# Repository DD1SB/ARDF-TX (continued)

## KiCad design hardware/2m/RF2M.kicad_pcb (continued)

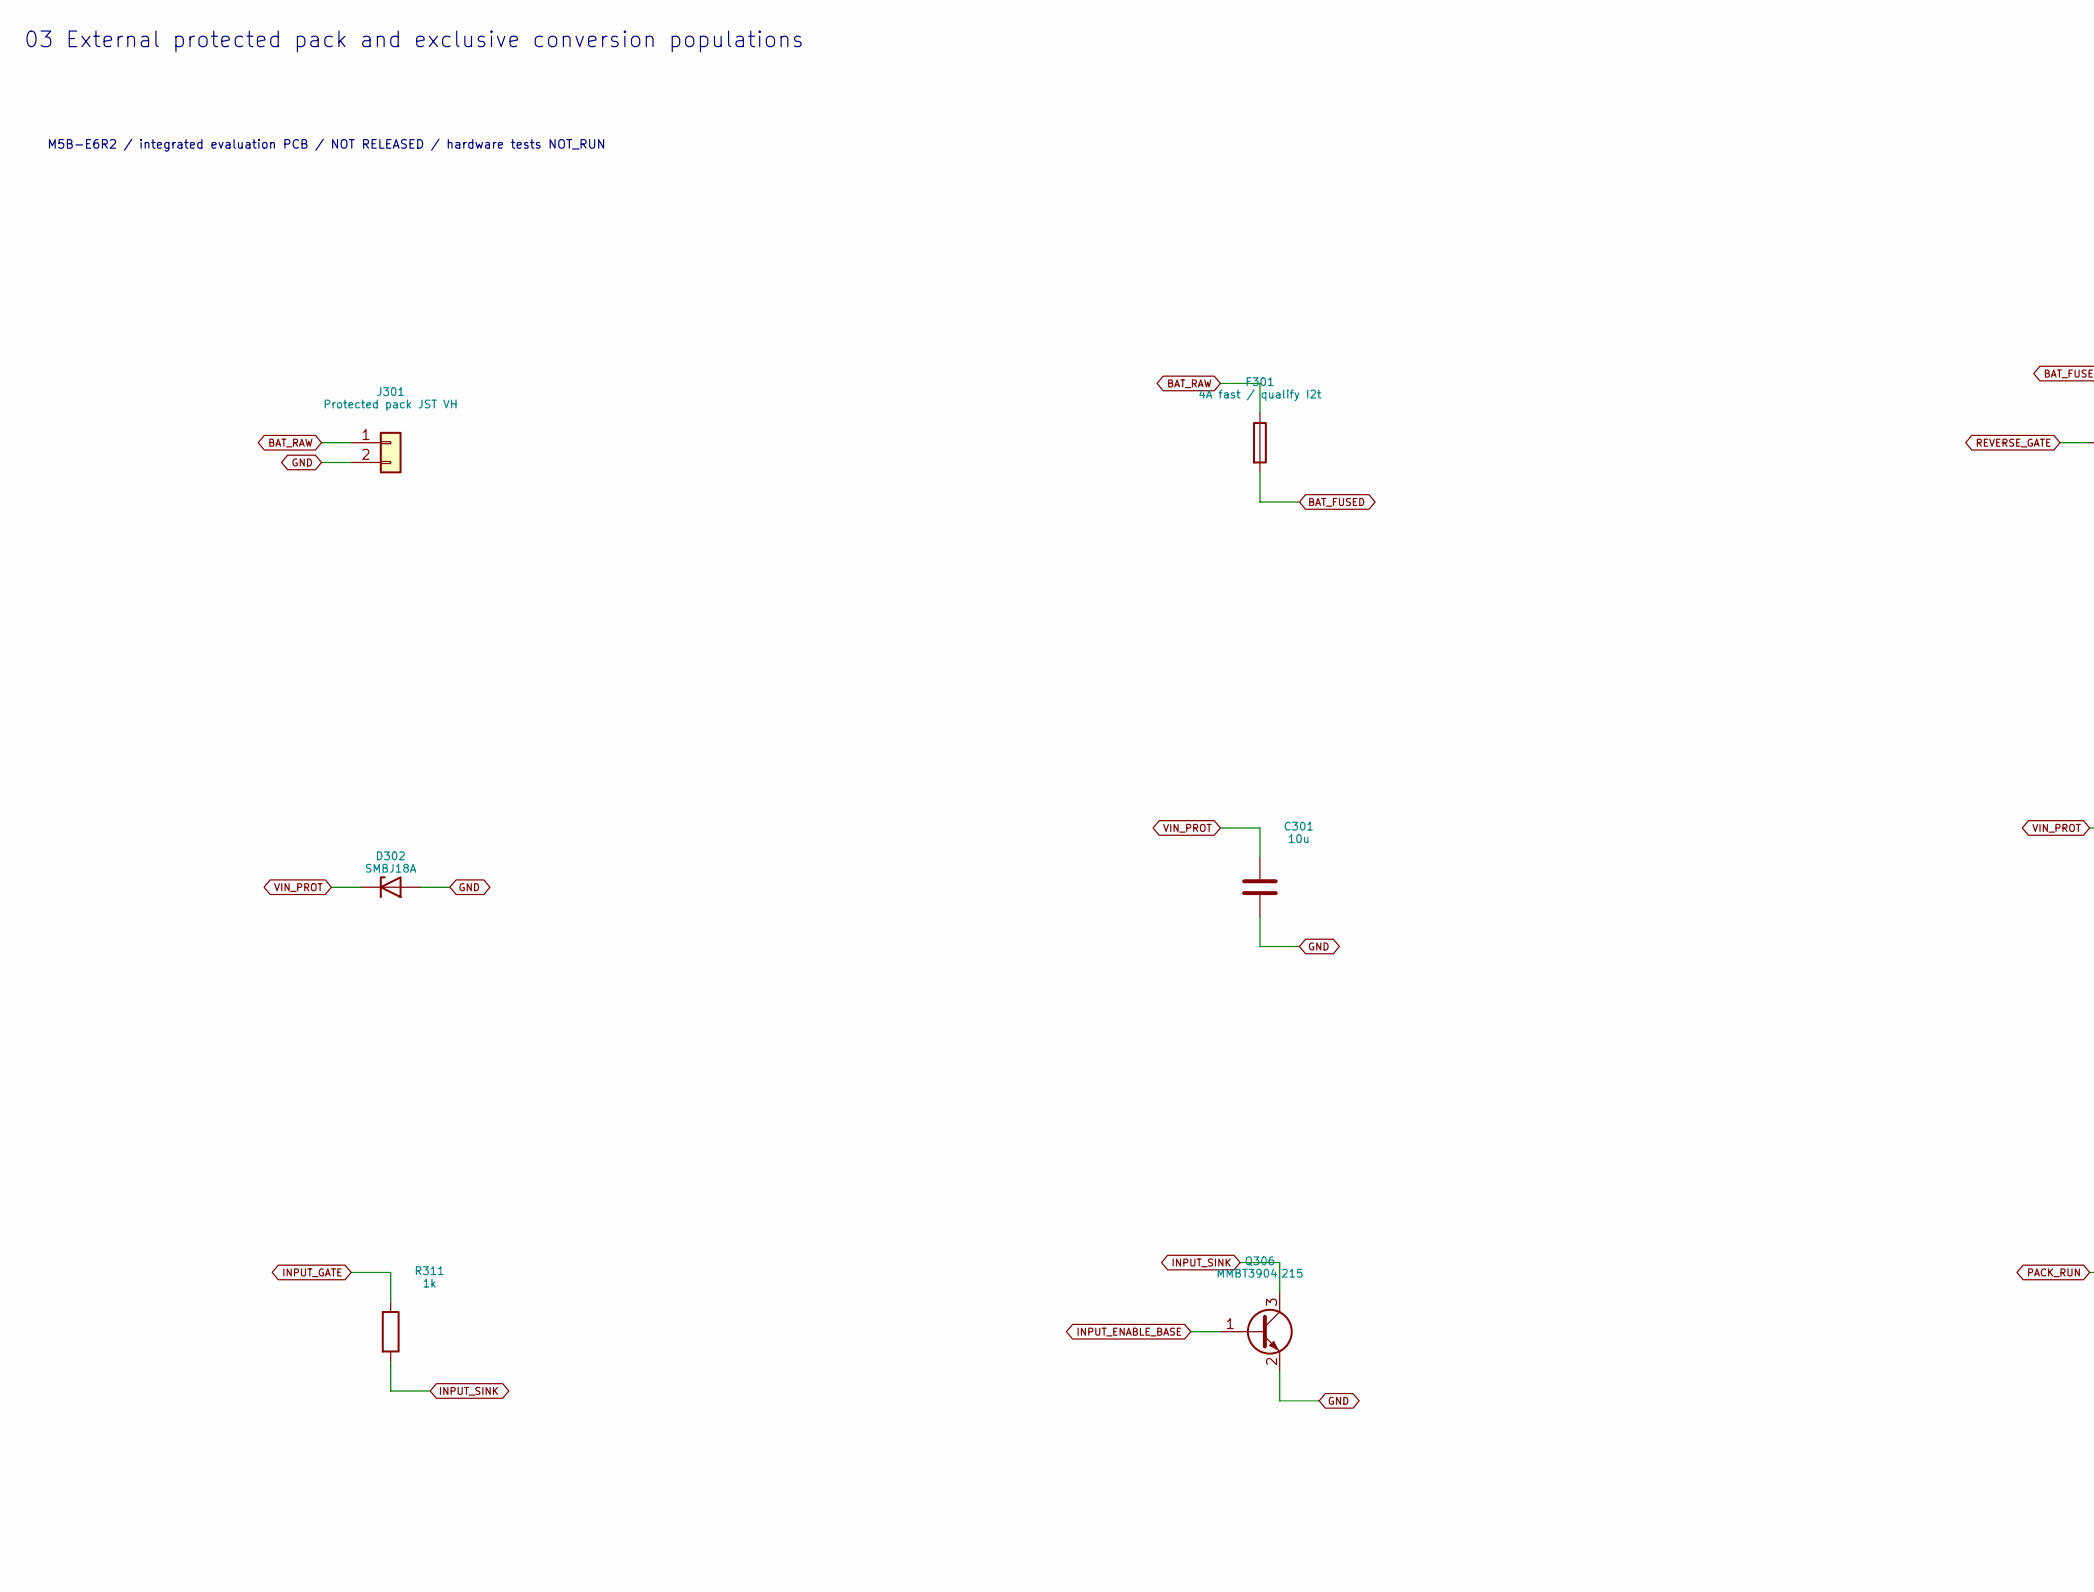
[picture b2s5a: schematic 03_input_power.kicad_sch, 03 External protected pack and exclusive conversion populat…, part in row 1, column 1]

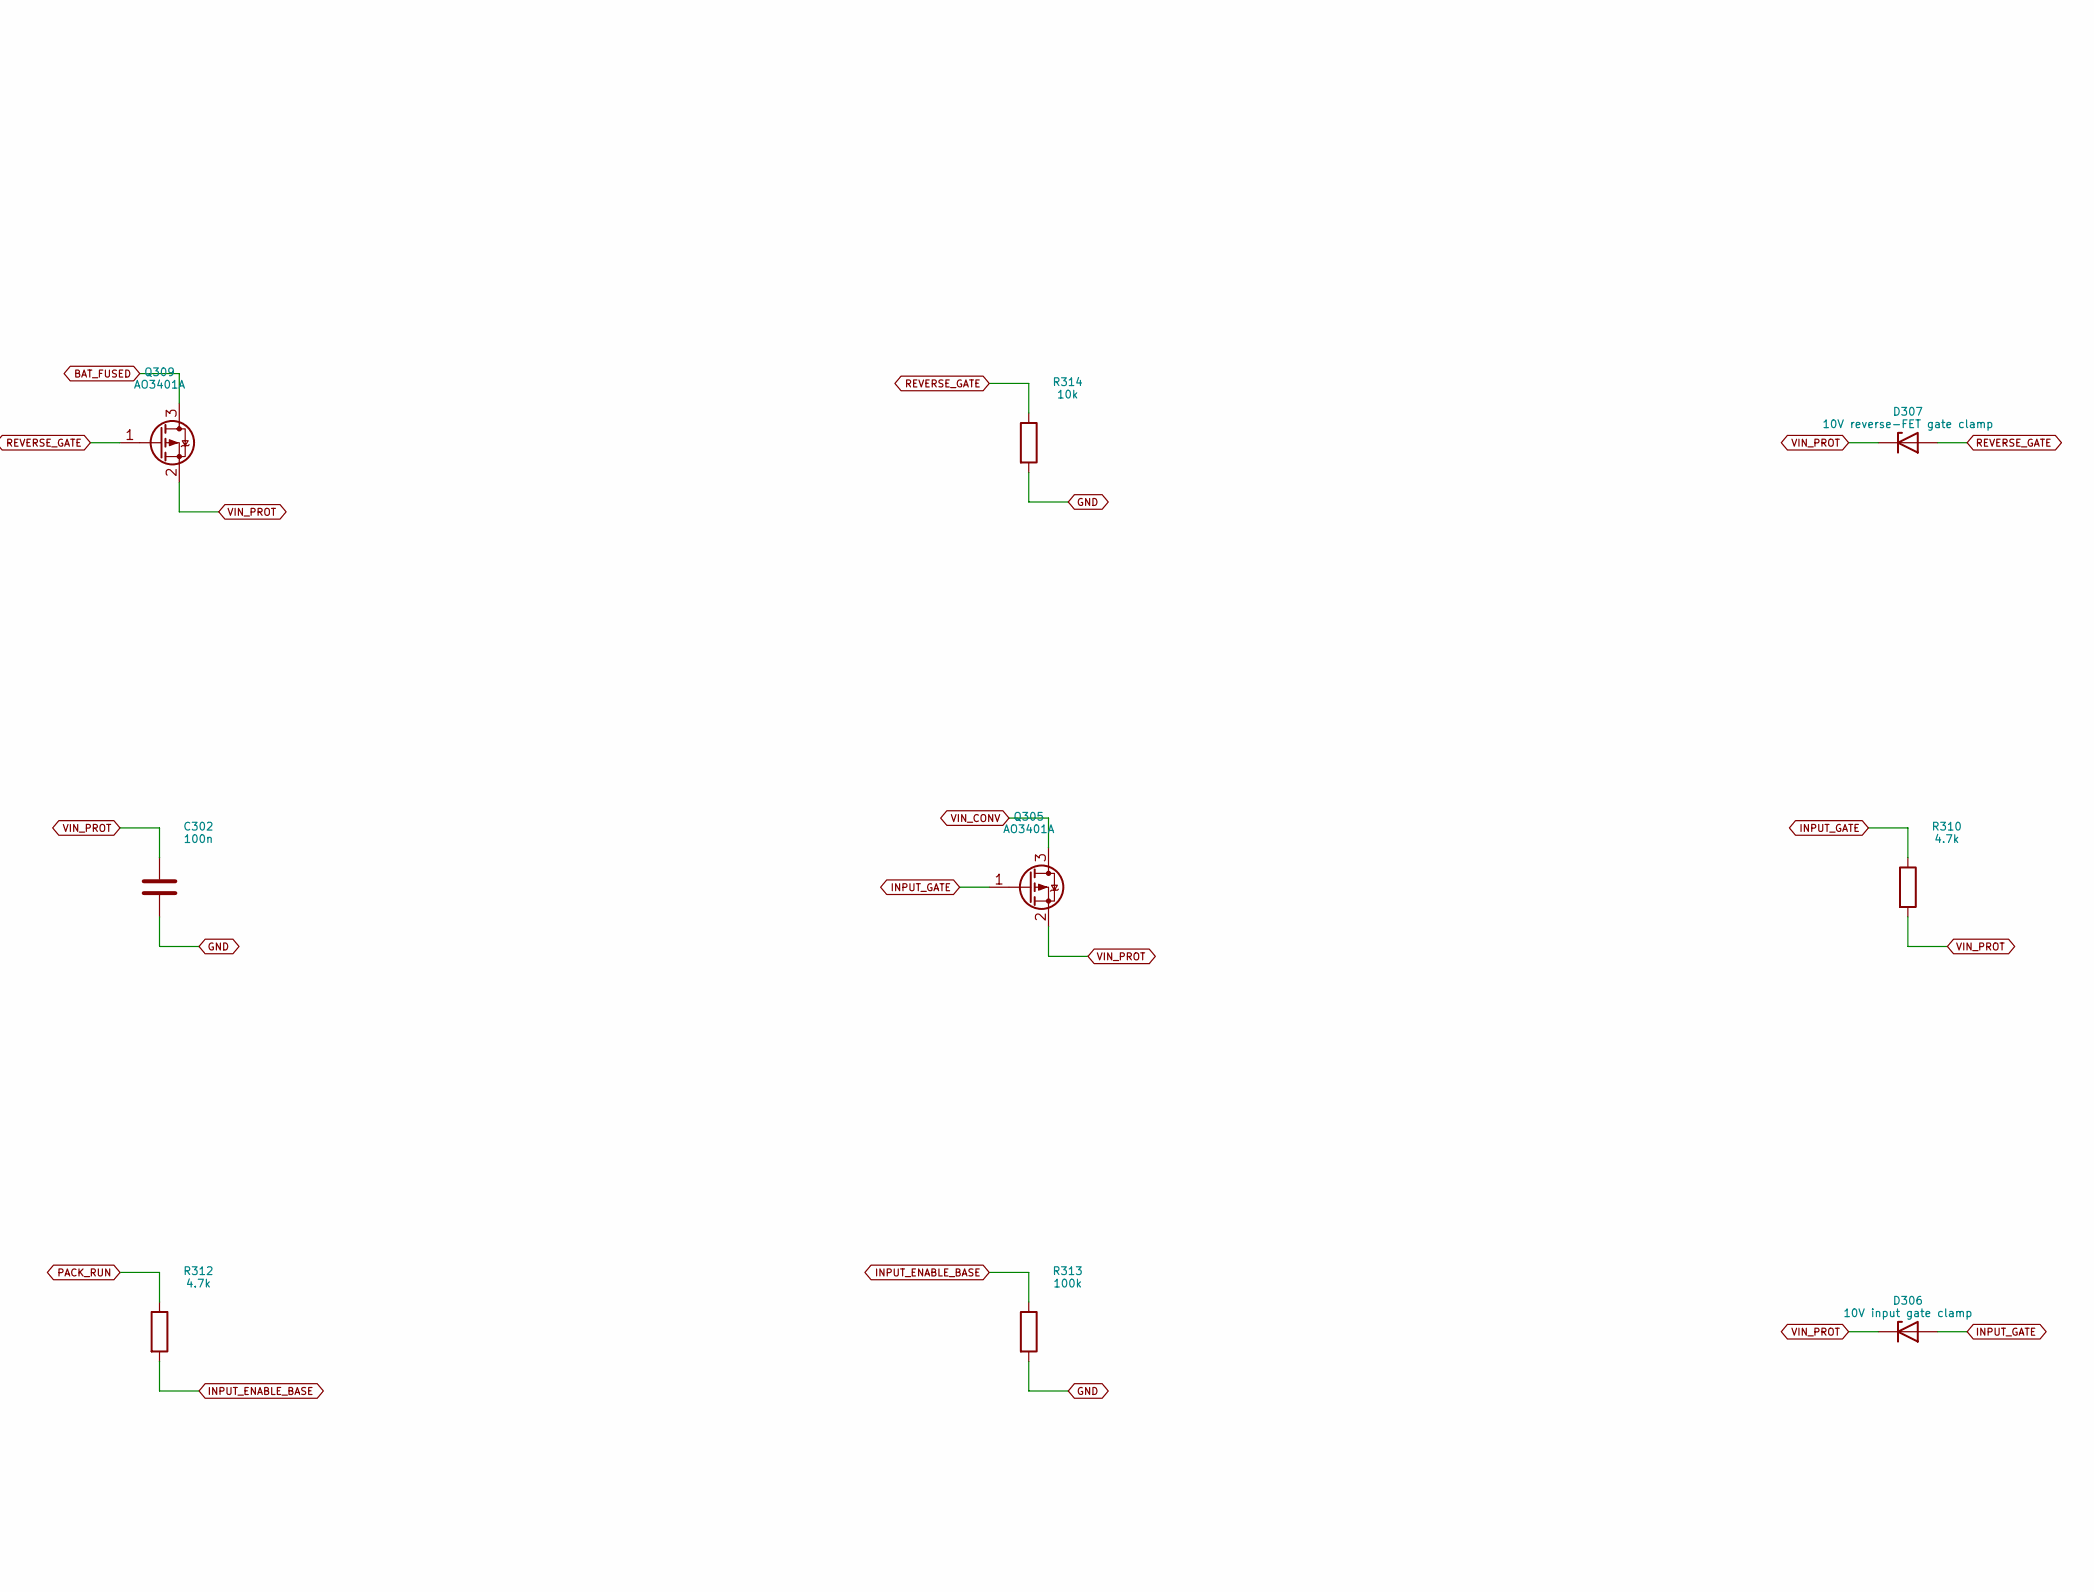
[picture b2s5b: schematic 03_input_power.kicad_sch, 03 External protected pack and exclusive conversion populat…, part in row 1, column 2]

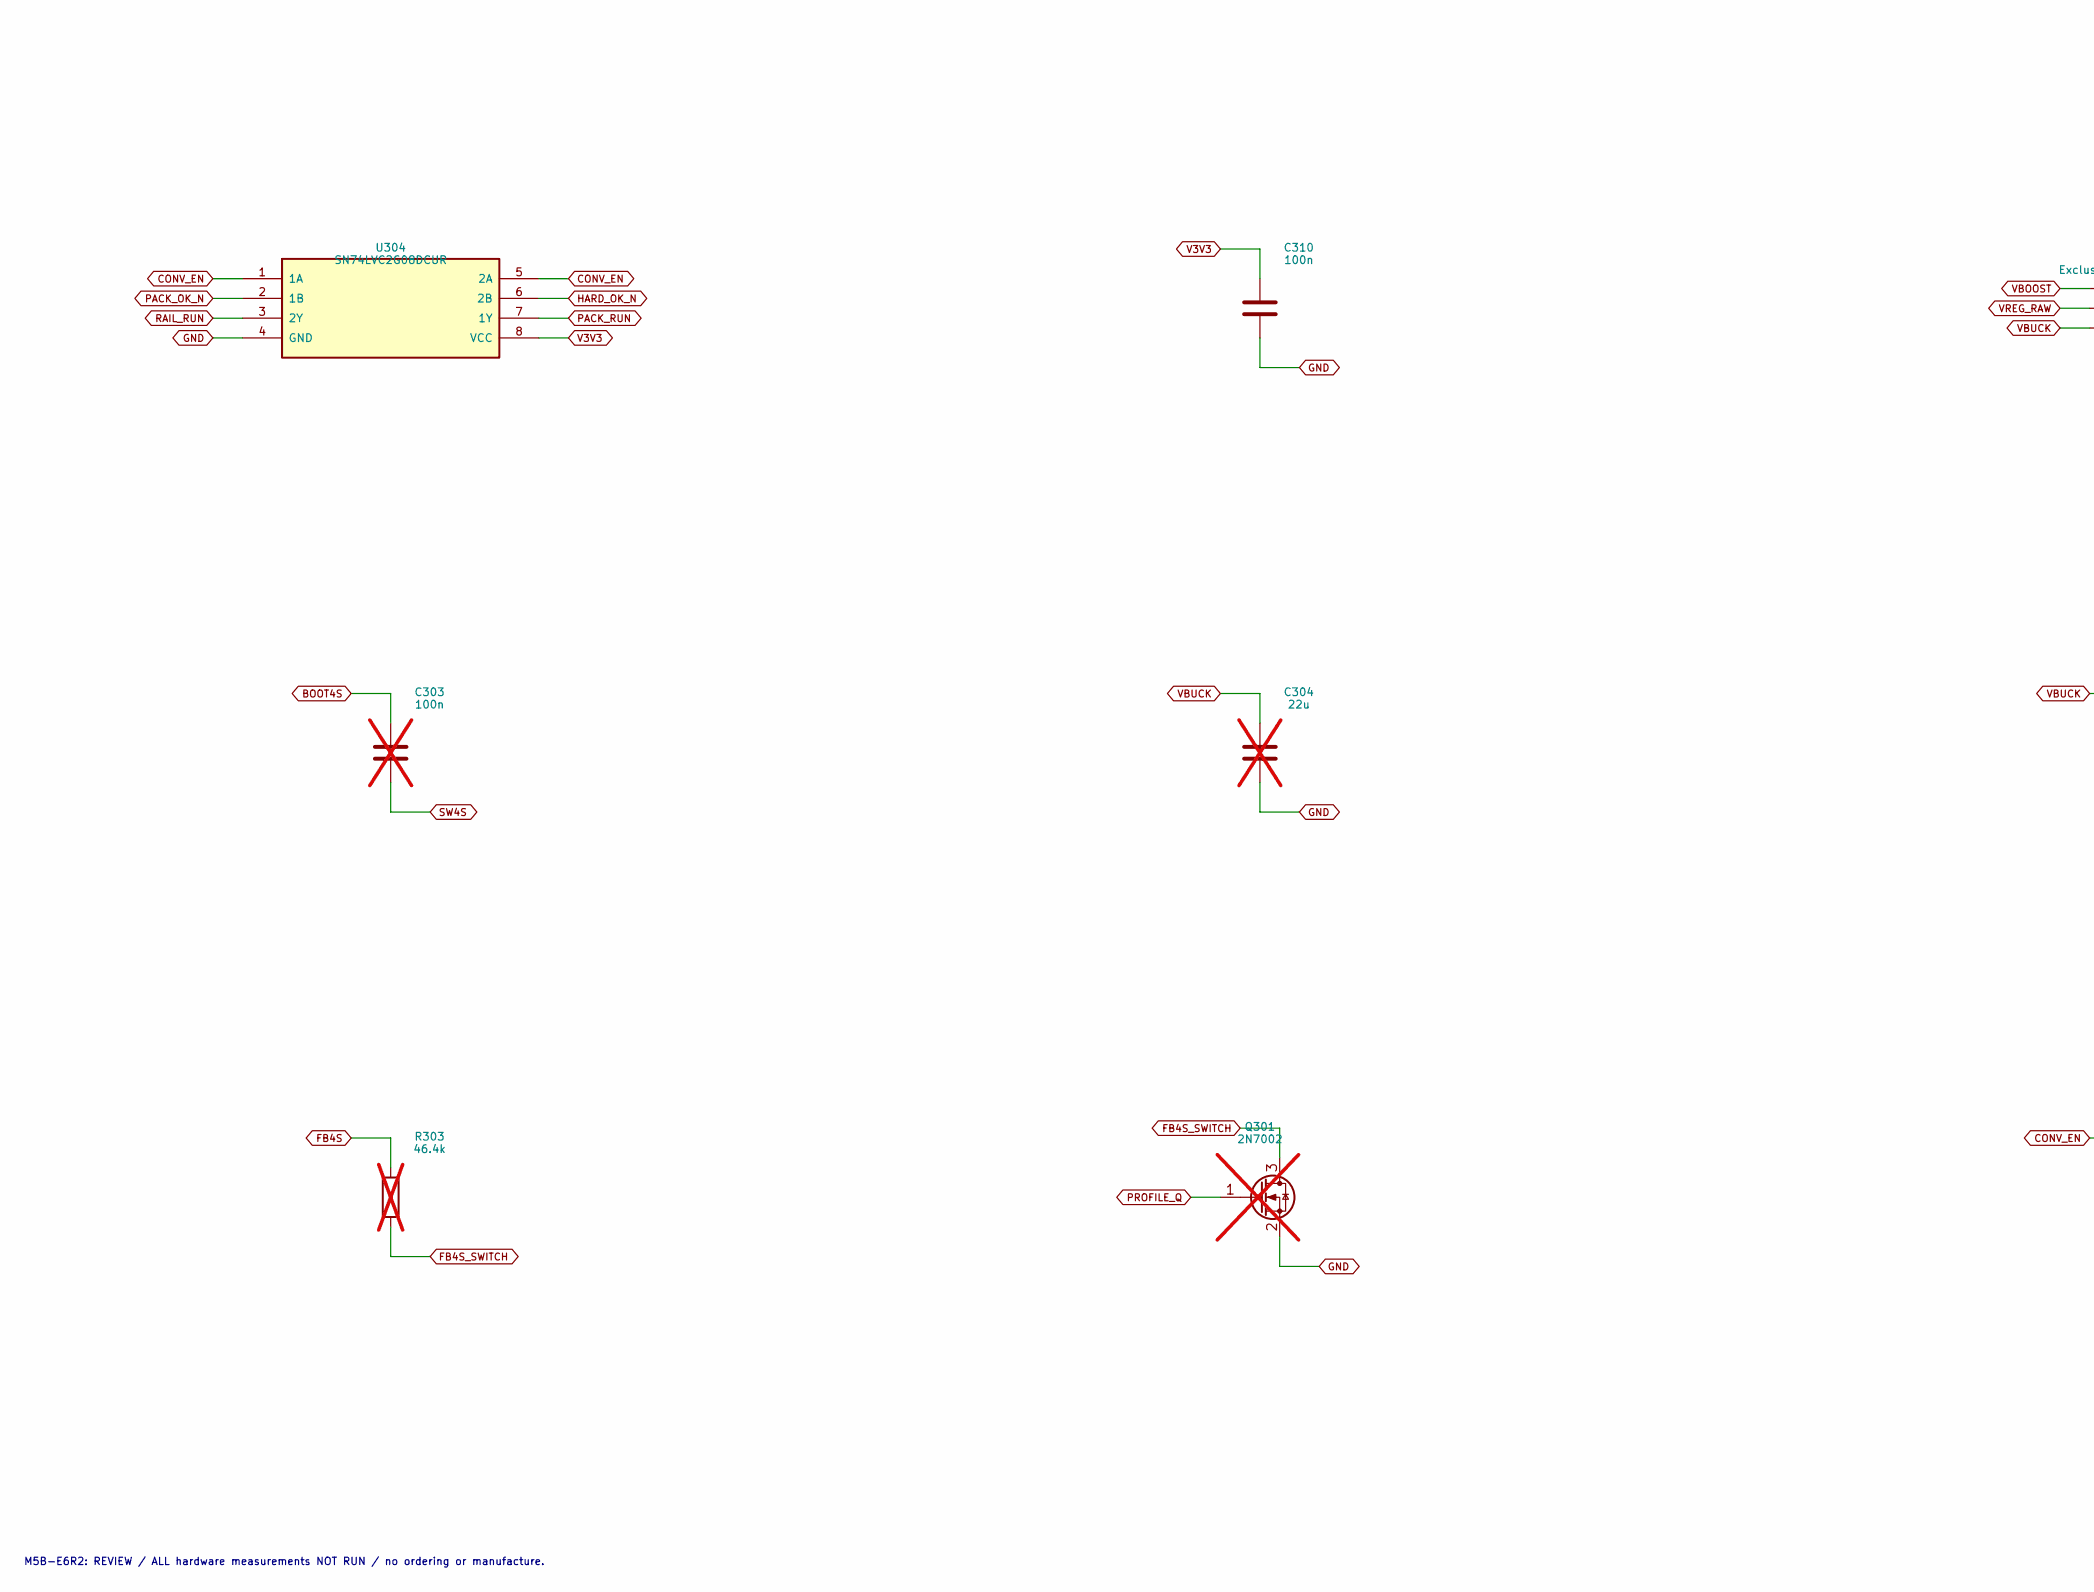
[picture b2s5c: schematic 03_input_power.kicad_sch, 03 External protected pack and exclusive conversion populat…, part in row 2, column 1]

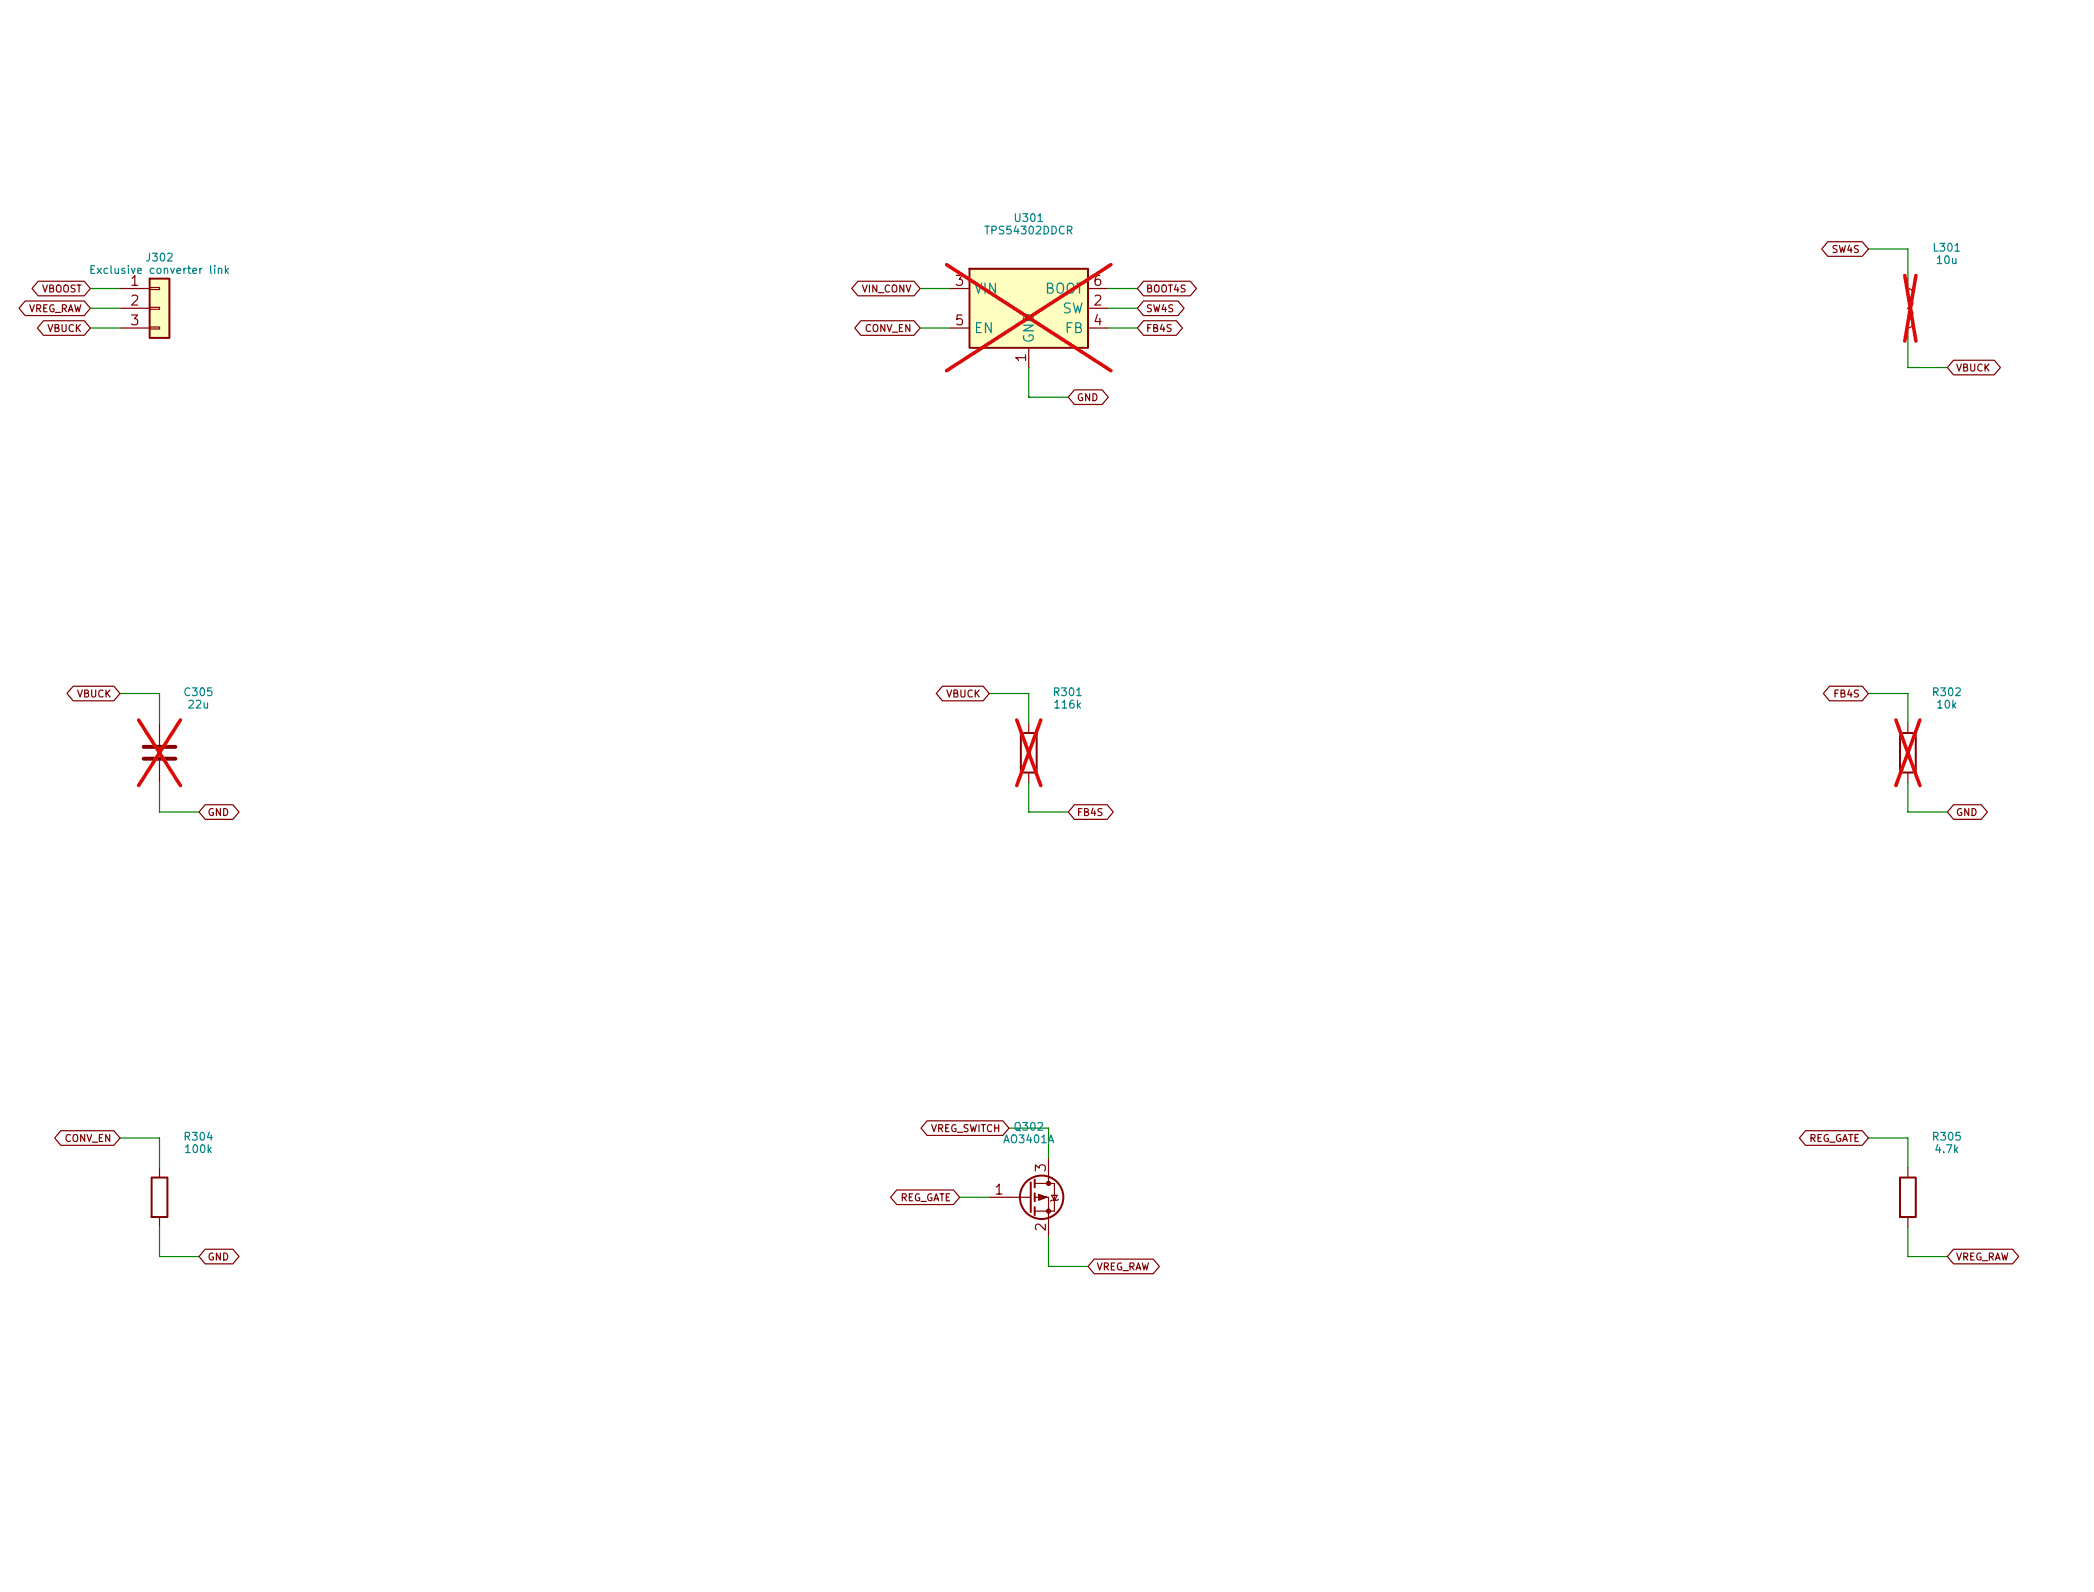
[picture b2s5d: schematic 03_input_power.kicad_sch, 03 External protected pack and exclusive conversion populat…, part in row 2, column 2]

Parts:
C301: 10u; C_1210_3225Metric_E3; MPN C3225X7R1V106M250AC
C302, C310: 100n; C_0603_1608Metric_E3; MPN CC0603KRX7R8BB104
C303: 100n; C_0603_1608Metric_E3; MPN CC0603KRX7R8BB104; not fitted
C304, C305: 22u; C_1210_3225Metric_E3; MPN GRM32ER71E226KE15L; not fitted
D302: SMBJ18A; D_SMB_E3; MPN SMBJ18A-E3/52
D306: 10V input gate clamp; D_SOD-123F_E3; MPN BZT52H-C10,115
D307: 10V reverse-FET gate clamp; D_SOD-123F_E3; MPN BZT52H-C10,115
F301: 4A fast / qualify I2t; Fuse_1206_3216Metric_E3; MPN 0466004.NRHF
J301: Protected pack JST VH; JST_VH_B2P-VH_1x02_P3.96mm_Vertical_E3; MPN B2P-VH(LF)(SN)
J302: Exclusive converter link; PinHeader_1x03_P2.54mm_Vertical_E3; MPN TSW-103-07-G-S
L301: 10u; Bourns_SRP1265A; MPN SRP1265A-100M; not fitted
Q301: 2N7002; SOT-23_E3; MPN 2N7002,215; not fitted
Q302, Q305, Q309: AO3401A; SOT-23_E3; MPN AO3401A
Q306: MMBT3904,215; SOT-23_E3; MPN MMBT3904,215
R301: 116k; R_0603_1608Metric_E3; MPN RC0603FR-07116KL; not fitted
R302: 10k; R_0603_1608Metric_E3; MPN RC0603FR-0710KL; not fitted
R303: 46.4k; R_0603_1608Metric_E3; MPN RC0603FR-0746K4L; not fitted
R304, R313: 100k; R_0603_1608Metric_E3; MPN RC0603FR-07100KL
R305, R310, R312: 4.7k; R_0603_1608Metric_E3; MPN RC0603FR-074K7L
R311: 1k; R_0603_1608Metric_E3; MPN RC0603FR-071KL
R314: 10k; R_0603_1608Metric_E3; MPN RC0603FR-0710KL
U301: TPS54302DDCR; SOT-23-6_Handsoldering_E3; MPN TPS54302DDCR; not fitted
U304: SN74LVC2G08DCUR; VSSOP-8_2.3x2mm_P0.5mm_E3; MPN SN74LVC2G08DCUR

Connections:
BAT_FUSED: F301.2, Q309.3 (D)
BAT_RAW: F301.1, J301.1
BOOT4S: C303.1, U301.6 (BOOT)
CONV_EN: R304.1, U301.5 (EN), U304.1 (1A), U304.5 (2A); also elsewhere on the board
FB4S: R301.2, R302.1, R303.1, U301.4 (FB)
FB4S_SWITCH: Q301.3 (D), R303.2
GND: C301.2, C302.2, C304.2, C305.2, C310.2, D302.2 (A), J301.2, Q301.2 (S), Q306.2 (E), R302.2, R304.2, R313.2, R314.2, U301.1 (GND), U304.4 (GND); also elsewhere on the board
HARD_OK_N: U304.6 (2B); also elsewhere on the board
INPUT_ENABLE_BASE: Q306.1 (B), R312.2, R313.1
INPUT_GATE: D306.2 (A), Q305.1 (G), R310.1, R311.1
INPUT_SINK: Q306.3 (C), R311.2
PACK_OK_N: U304.2 (1B); also elsewhere on the board
PACK_RUN: R312.1, U304.7 (1Y)
PROFILE_Q: Q301.1 (G); also elsewhere on the board
RAIL_RUN: U304.3 (2Y); also elsewhere on the board
REG_GATE: Q302.1 (G), R305.1; also elsewhere on the board
REVERSE_GATE: D307.2 (A), Q309.1 (G), R314.1
SW4S: C303.2, L301.1, U301.2 (SW)
V3V3: C310.1, U304.8 (VCC); also elsewhere on the board
VBOOST: J302.1; also elsewhere on the board
VBUCK: C304.1, C305.1, J302.3, L301.2, R301.1
VIN_CONV: Q305.3 (D), U301.3 (VIN); also elsewhere on the board
VIN_PROT: C301.1, C302.1, D302.1 (K), D306.1 (K), D307.1 (K), Q305.2 (S), Q309.2 (S), R310.2; also elsewhere on the board
VREG_RAW: J302.2, Q302.2 (S), R305.2; also elsewhere on the board
VREG_SWITCH: Q302.3 (D); also elsewhere on the board

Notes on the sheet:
03 External protected pack and exclusive conversion populations
M5B-E6R2 / integrated evaluation PCB / NOT RELEASED / hardware tests NOT_RUN
M5B-E6R2: REVIEW / ALL hardware measurements NOT RUN / no ordering or manufacture.

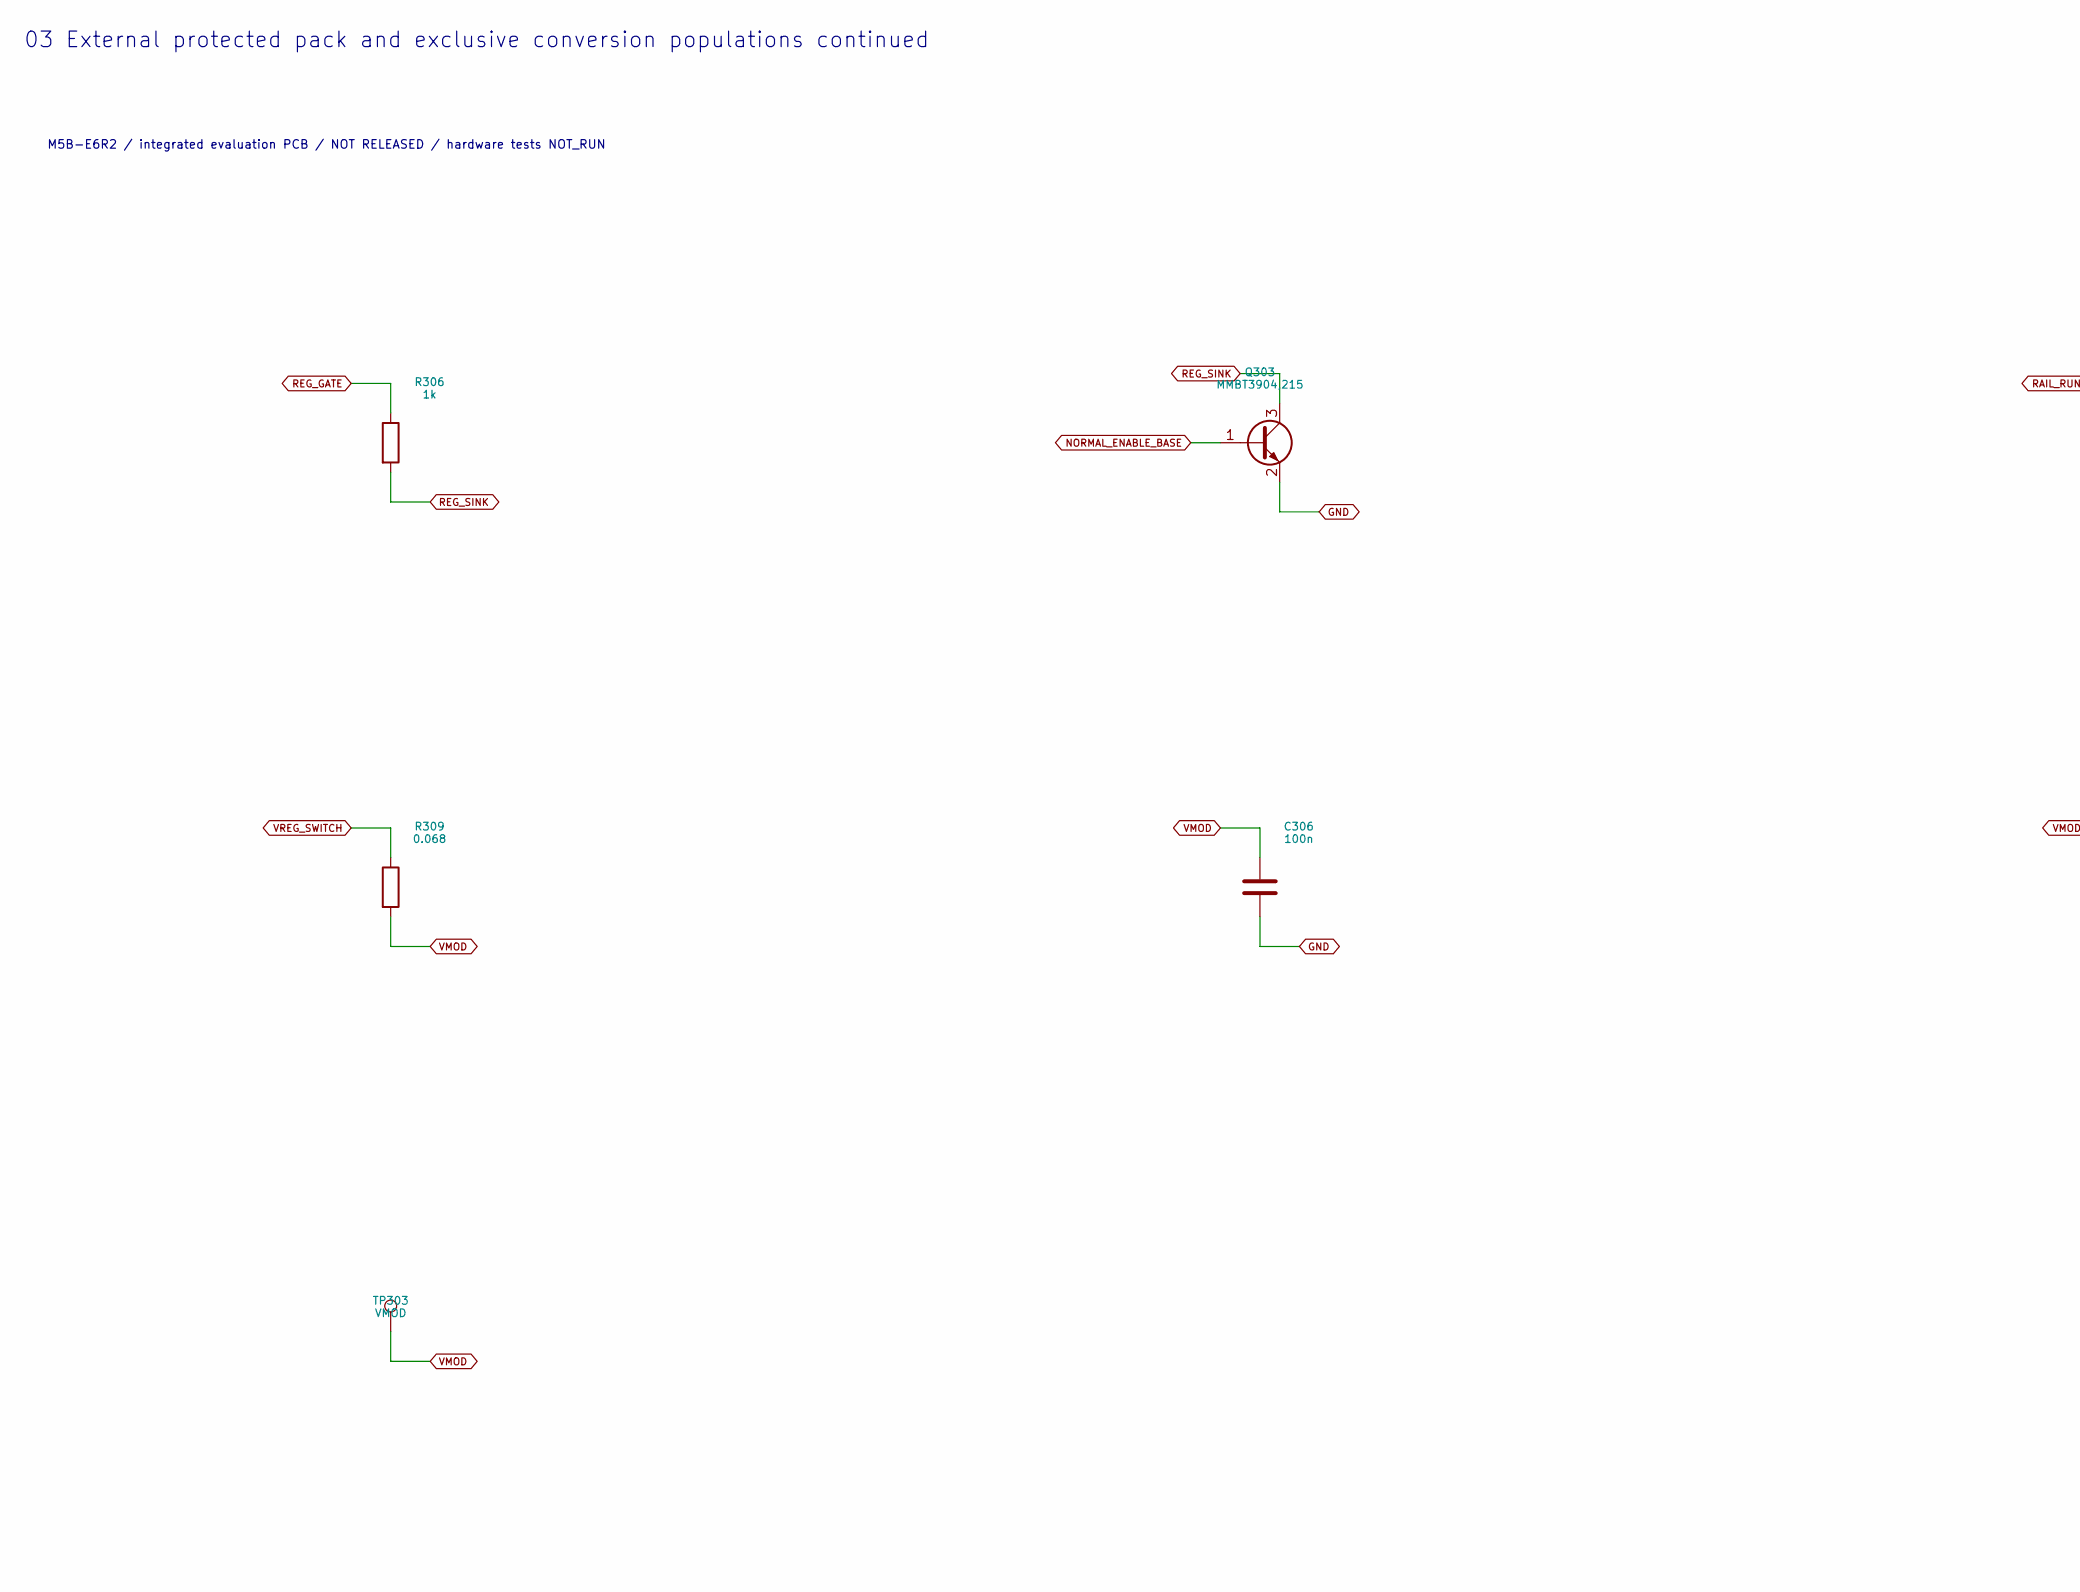
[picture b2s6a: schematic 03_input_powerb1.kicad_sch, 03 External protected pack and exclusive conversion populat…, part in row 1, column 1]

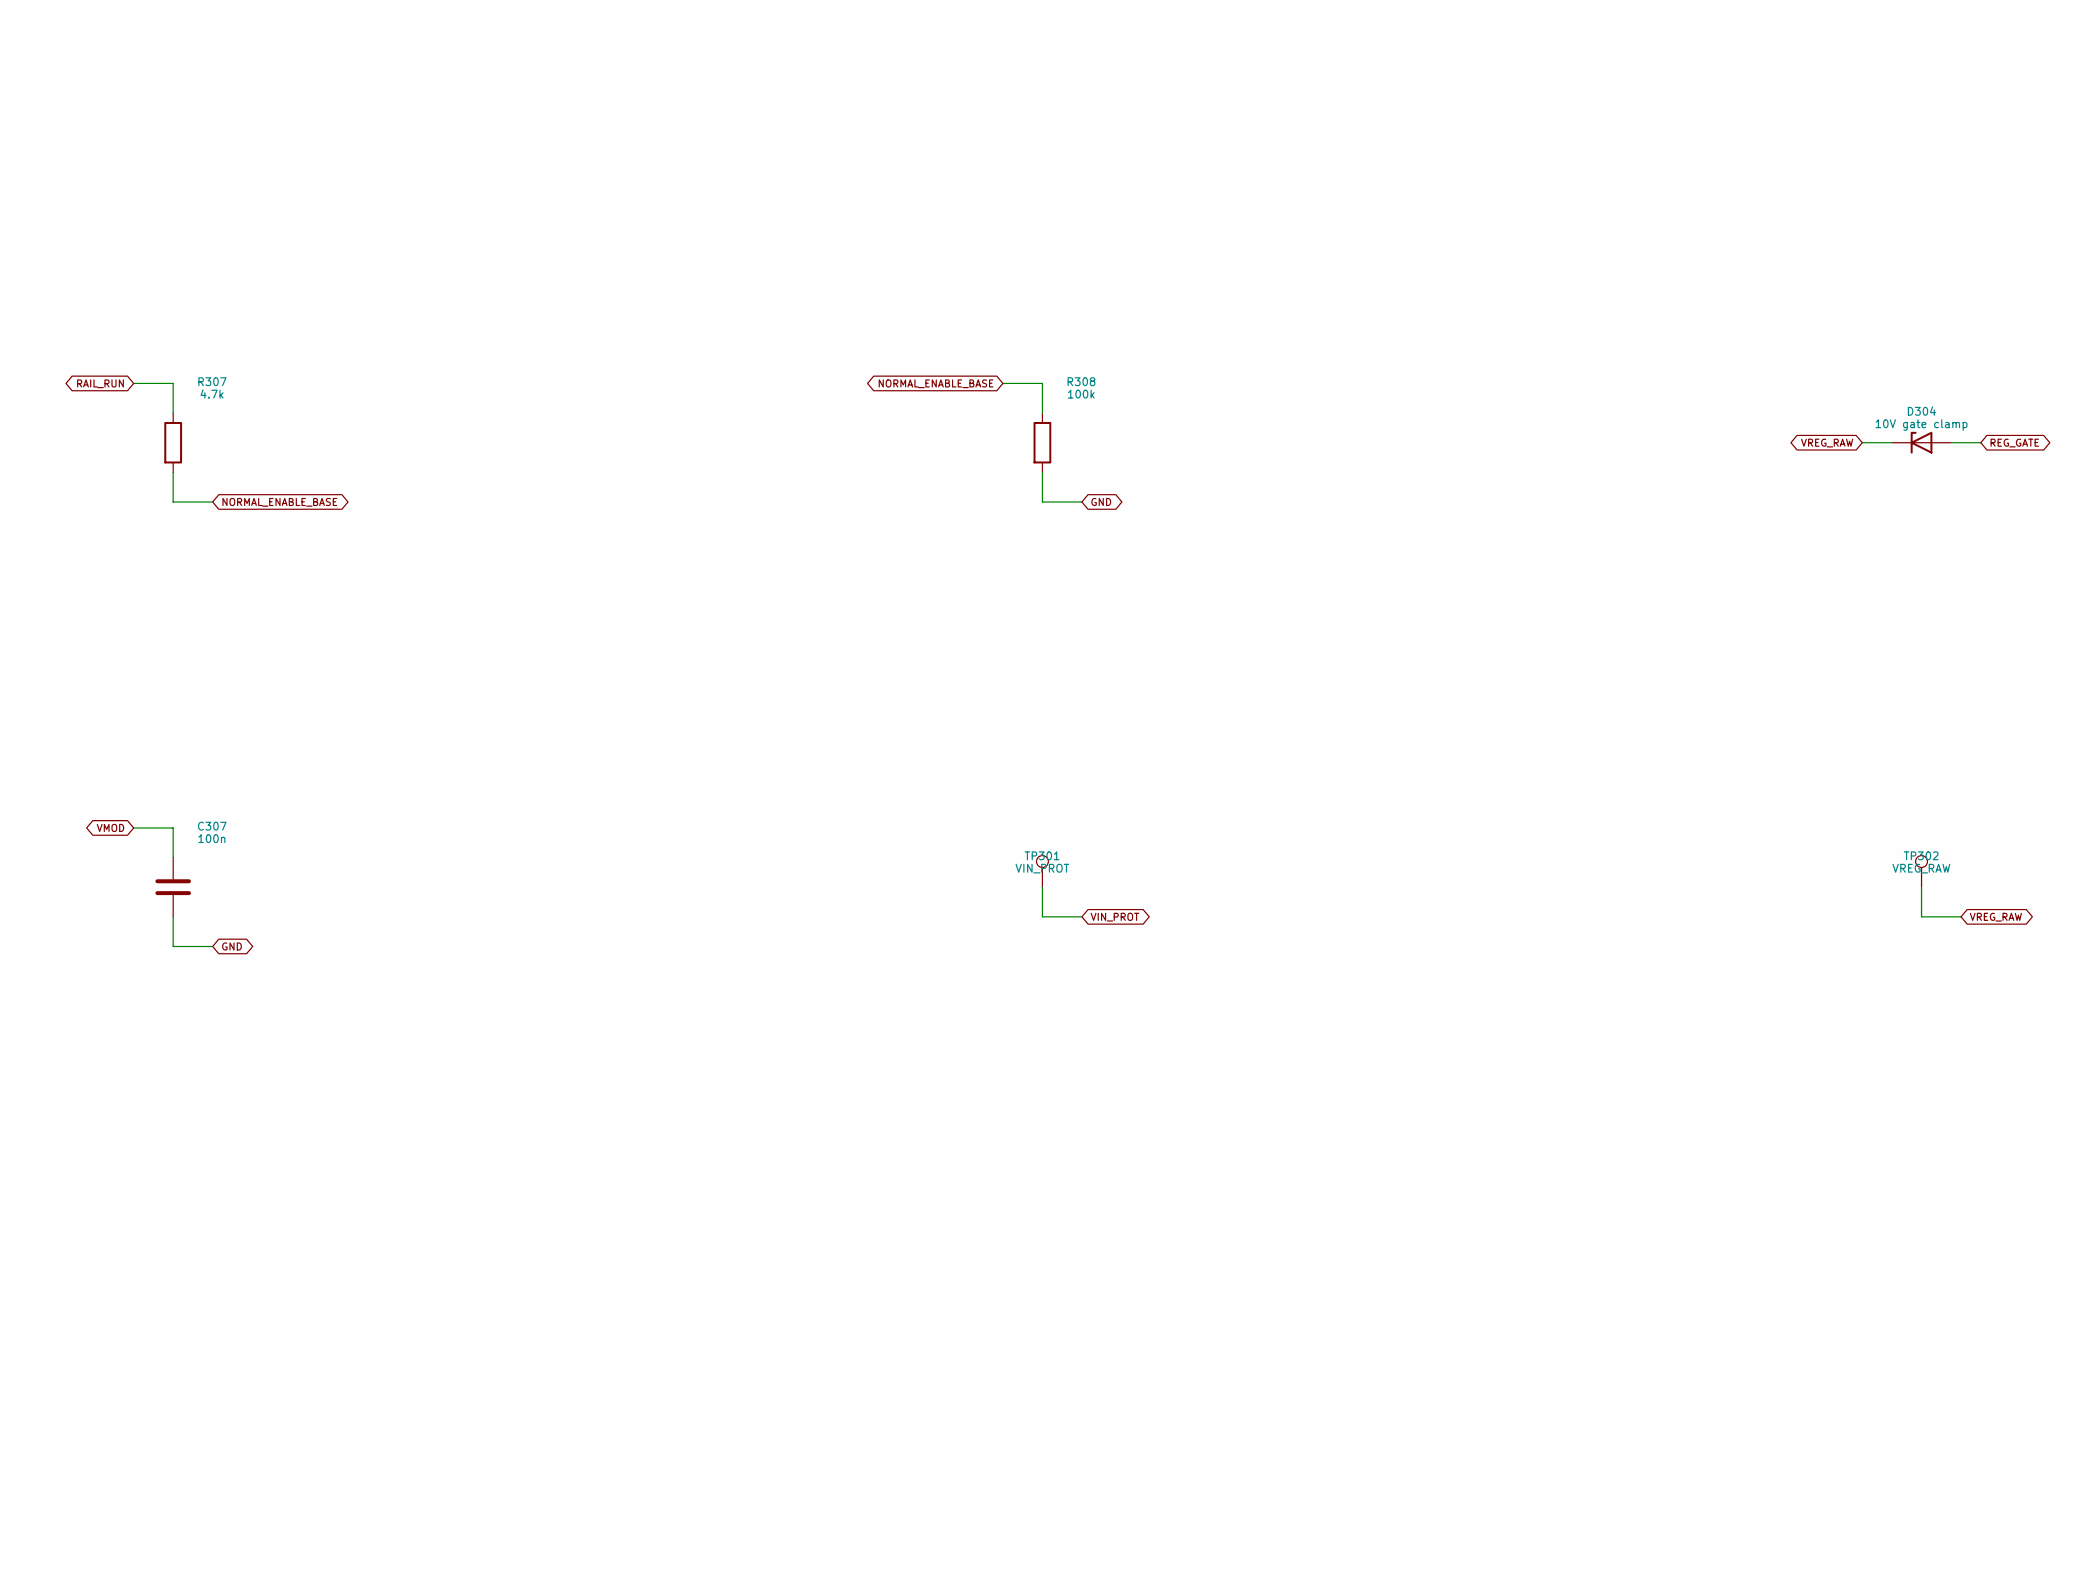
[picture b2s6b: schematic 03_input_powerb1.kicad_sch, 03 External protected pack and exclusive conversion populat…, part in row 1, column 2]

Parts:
C306, C307: 100n; C_0603_1608Metric_E3; MPN CC0603KRX7R8BB104
D304: 10V gate clamp; D_SOD-123F_E3; MPN BZT52H-C10,115
Q303: MMBT3904,215; SOT-23_E3; MPN MMBT3904,215
R306: 1k; R_0603_1608Metric_E3; MPN RC0603FR-071KL
R307: 4.7k; R_0603_1608Metric_E3; MPN RC0603FR-074K7L
R308: 100k; R_0603_1608Metric_E3; MPN RC0603FR-07100KL
R309: 0.068; R_2512_6332Metric_E3; MPN WSL2512R0680FEA
TP301: VIN_PROT; TestPoint_Pad_D1.0mm_E3; MPN PCB feature
TP302: VREG_RAW; TestPoint_Pad_D1.0mm_E3; MPN PCB feature
TP303: VMOD; TestPoint_Pad_D1.0mm_E3; MPN PCB feature

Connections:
GND: C306.2, C307.2, Q303.2 (E), R308.2; also elsewhere on the board
NORMAL_ENABLE_BASE: Q303.1 (B), R307.2, R308.1
RAIL_RUN: R307.1; also elsewhere on the board
REG_GATE: D304.2 (A), R306.1; also elsewhere on the board
REG_SINK: Q303.3 (C), R306.2
VIN_PROT: TP301.1; also elsewhere on the board
VMOD: C306.1, C307.1, R309.2, TP303.1; also elsewhere on the board
VREG_RAW: D304.1 (K), TP302.1; also elsewhere on the board
VREG_SWITCH: R309.1; also elsewhere on the board

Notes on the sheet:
03 External protected pack and exclusive conversion populations continued
M5B-E6R2 / integrated evaluation PCB / NOT RELEASED / hardware tests NOT_RUN
M5B-E6R2: REVIEW / ALL hardware measurements NOT RUN / no ordering or manufacture.
